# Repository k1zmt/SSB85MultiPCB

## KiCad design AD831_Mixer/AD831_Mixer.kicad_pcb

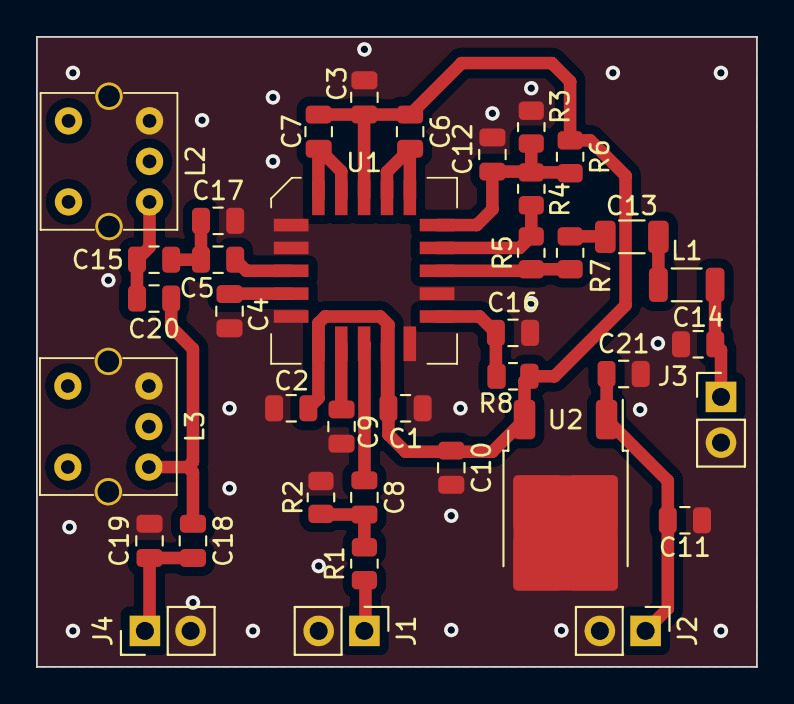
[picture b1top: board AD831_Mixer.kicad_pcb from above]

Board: 2 copper layers, 40.0 x 35.0 mm, 38 parts (0 on the bottom side), 22 nets.

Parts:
C1, C2, C3, C4, C5, C6, C7, C8, C9, C11, C12, C14, C16: 104; C_0805_2012Metric
C10, C21: 105; C_0805_2012Metric
C13: 104; C_1206_3216Metric
C15, C18: 820; C_0805_2012Metric
C17, C19: 751; C_0805_2012Metric
C20: 7.5p; C_0805_2012Metric
J1, J4: Conn_Coaxial; PinHeader_1x02_P2.54mm_Vertical
J2, J3: Conn_01x02; PinHeader_1x02_P2.54mm_Vertical
L1: L_Ferrite; L_1206_3216Metric
L2, L3: L_Core_Ferrite_Coupled_12345; L_Coilcraft_Slot7_15
R1: 221; R_0805_2012Metric
R2: 510; R_0805_2012Metric
R3, R6, R8: 472; R_0805_2012Metric
R4: 51R; R_0805_2012Metric
R5: 111; R_0805_2012Metric
R7: 102; R_0805_2012Metric
U1: AD831AP; PLCC-20
U2: LM78M05_TO252; TO-252-2

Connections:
+9V: C1.2, C2.2, C3.2, C6.1, C7.1, C10.1, R6.1, R8.2, U1.1 (VP), U1.9 (VP), U1.12 (VP), U2.3 (VO)
Earth: C1.1, C2.1, C3.1, C4.2, C9.2, C10.2, C11.2, C12.2, C14.2, C16.2, C17.2, C19.2, C21.2, J1.2 (Ext), J2.2, J3.2, J4.2 (Ext), L2.3, L2.MP, L3.3, L3.MP, R2.1, R3.1, U1.4 (GND), U1.5 (VN), U1.8 (VN), U1.13 (GND), U1.15 (VN), U2.2 (GND)
unnamed: C8.1, R1.2, R2.2
unnamed: C13.1, L1.1
unnamed: C13.2, R7.1
unnamed: C15.1, C20.2, L2.1
unnamed: C5.2, C15.2, C17.1
unnamed: C18.1, C20.1, L3.1
unnamed: J1.1 (In), R1.1
unnamed: C11.1, C21.1, J2.1, U2.1 (VI)
unnamed: C14.1, J3.1, L1.2
unnamed: C18.2, C19.1, J4.1 (In)
unnamed: C7.2, U1.2 (IFN), U1.3 (AN)
unnamed: C6.2, U1.19 (AP), U1.20 (IFP)
unnamed: C16.1, R8.1, U1.14 (BIAS)
unnamed: C12.1, R3.2, R4.1, R6.2, U1.18 (COM)
unnamed: C9.1, U1.10 (LON)
unnamed: C8.2, U1.11 (LOP)
unnamed: R5.2, R7.2, U1.16 (OUT)
unnamed: C4.1, U1.7 (RFN)
unnamed: C5.1, U1.6 (RFP)
unnamed: R4.2, R5.1, U1.17 (VFB)

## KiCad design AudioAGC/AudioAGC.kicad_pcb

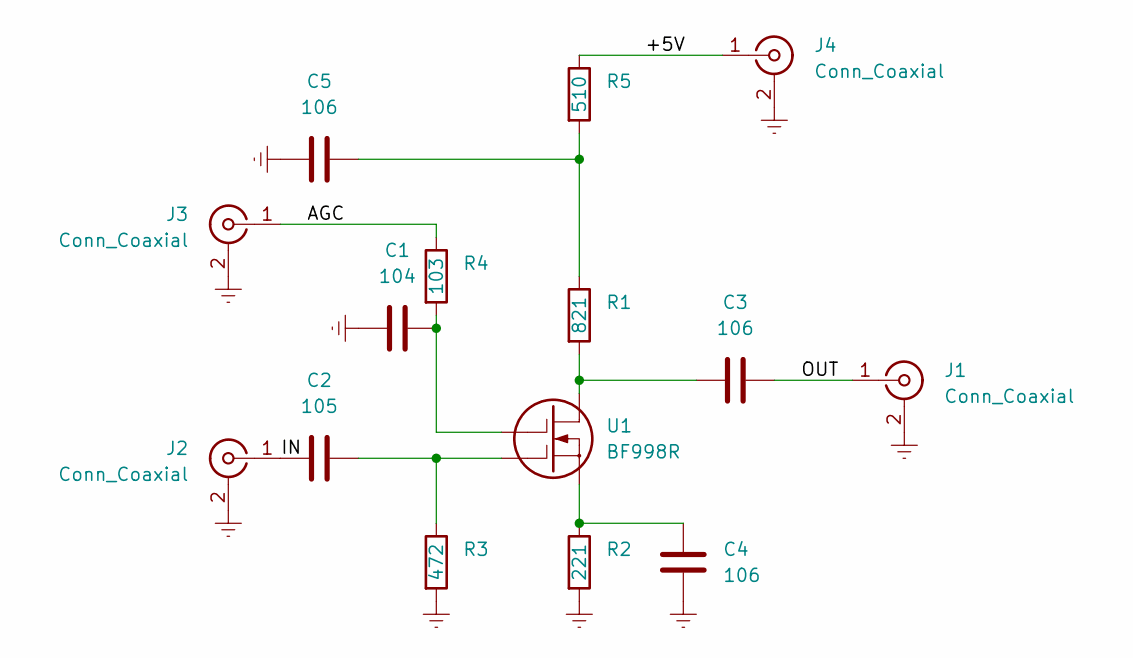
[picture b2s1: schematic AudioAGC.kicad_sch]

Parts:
C1: 104; C_0805_2012Metric
C2: 105; C_0805_2012Metric
C3, C4, C5: 106; C_0805_2012Metric
J1, J2, J3, J4: Conn_Coaxial; U.FL_Hirose_U.FL-R-SMT-1_Vertical
R1: 821; R_0805_2012Metric
R2: 221; R_0805_2012Metric
R3: 472; R_0805_2012Metric
R4: 103; R_0805_2012Metric
R5: 510; R_0805_2012Metric
U1: BF998R; SOT-143R

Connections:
/+5V: J4.1 (In), R5.1
/AGC: J3.1 (In), R4.1
/IN: C2.1, J2.1 (In)
/OUT: C3.2, J1.1 (In)
Earth: C1.1, C4.1, C5.1, J1.2 (Ext), J2.2 (Ext), J3.2 (Ext), J4.2 (Ext), R2.2, R3.2
unnamed: C5.2, R1.1, R5.2
unnamed: C3.1, R1.2, U1.2 (D)
unnamed: C2.2, R3.1, U1.4 (G1)
unnamed: C1.2, R4.2, U1.3 (G2)
unnamed: C4.2, R2.1, U1.1 (S)

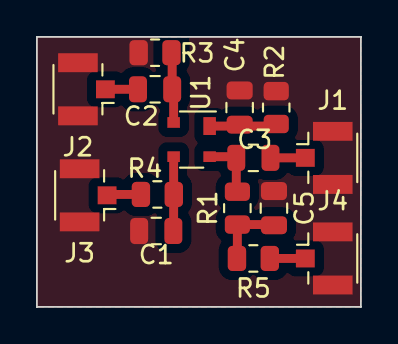
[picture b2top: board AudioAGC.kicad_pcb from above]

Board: 2 copper layers, 18.0 x 15.0 mm, 15 parts (0 on the bottom side), 10 nets.

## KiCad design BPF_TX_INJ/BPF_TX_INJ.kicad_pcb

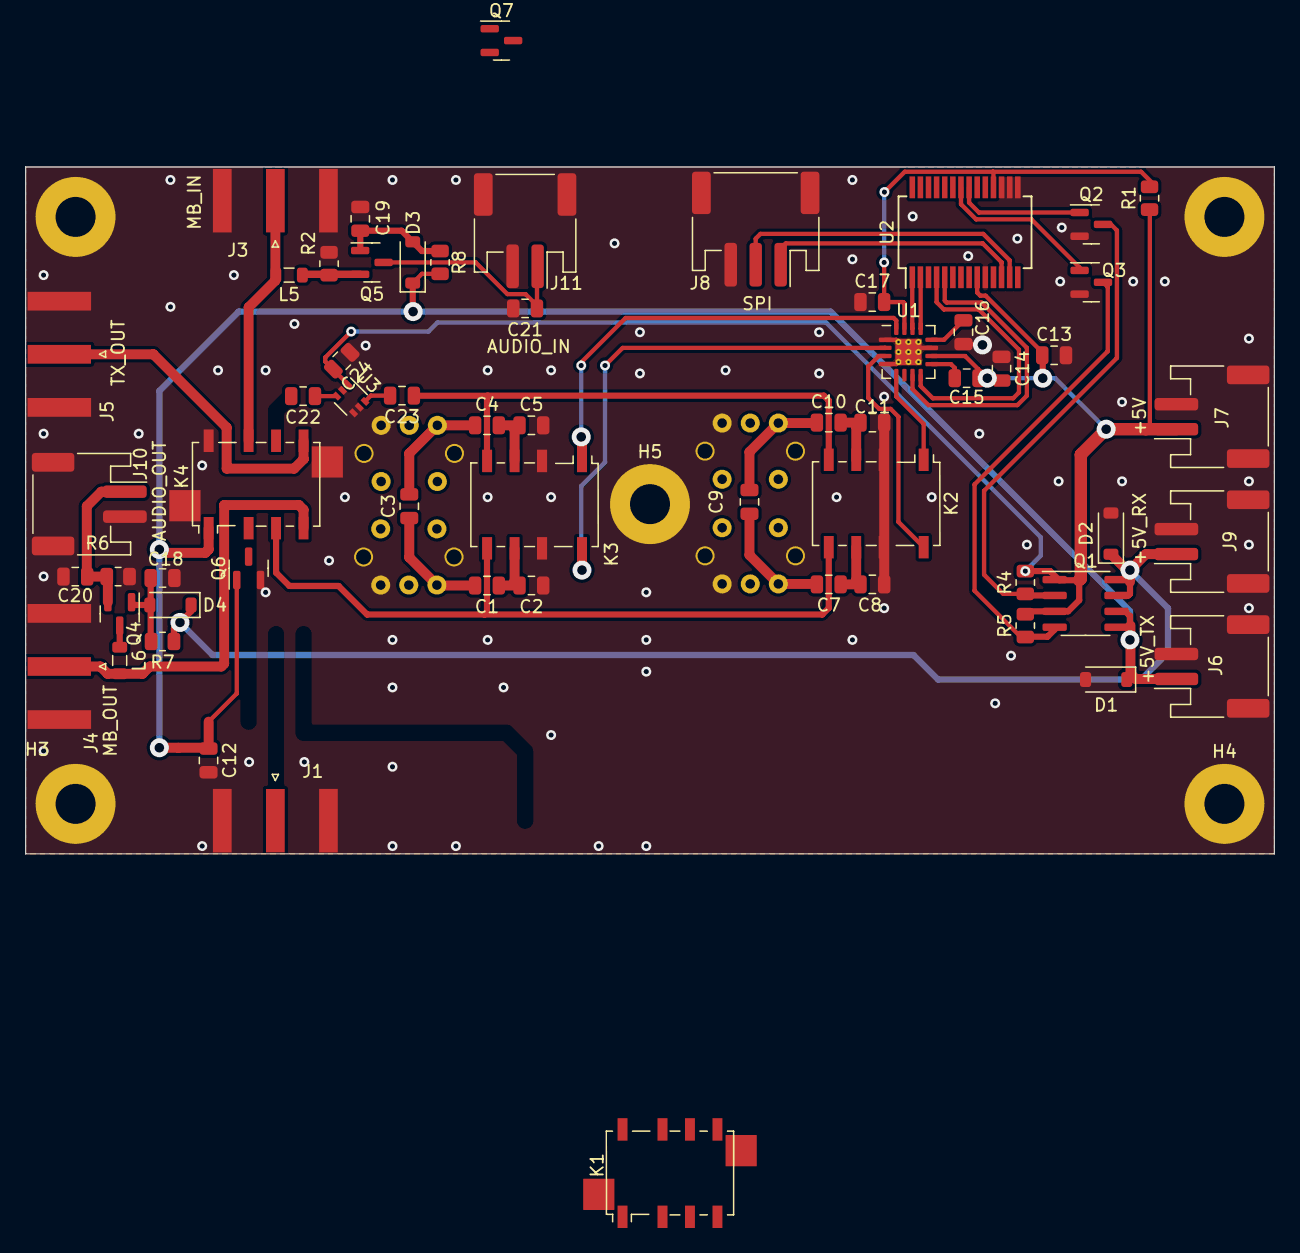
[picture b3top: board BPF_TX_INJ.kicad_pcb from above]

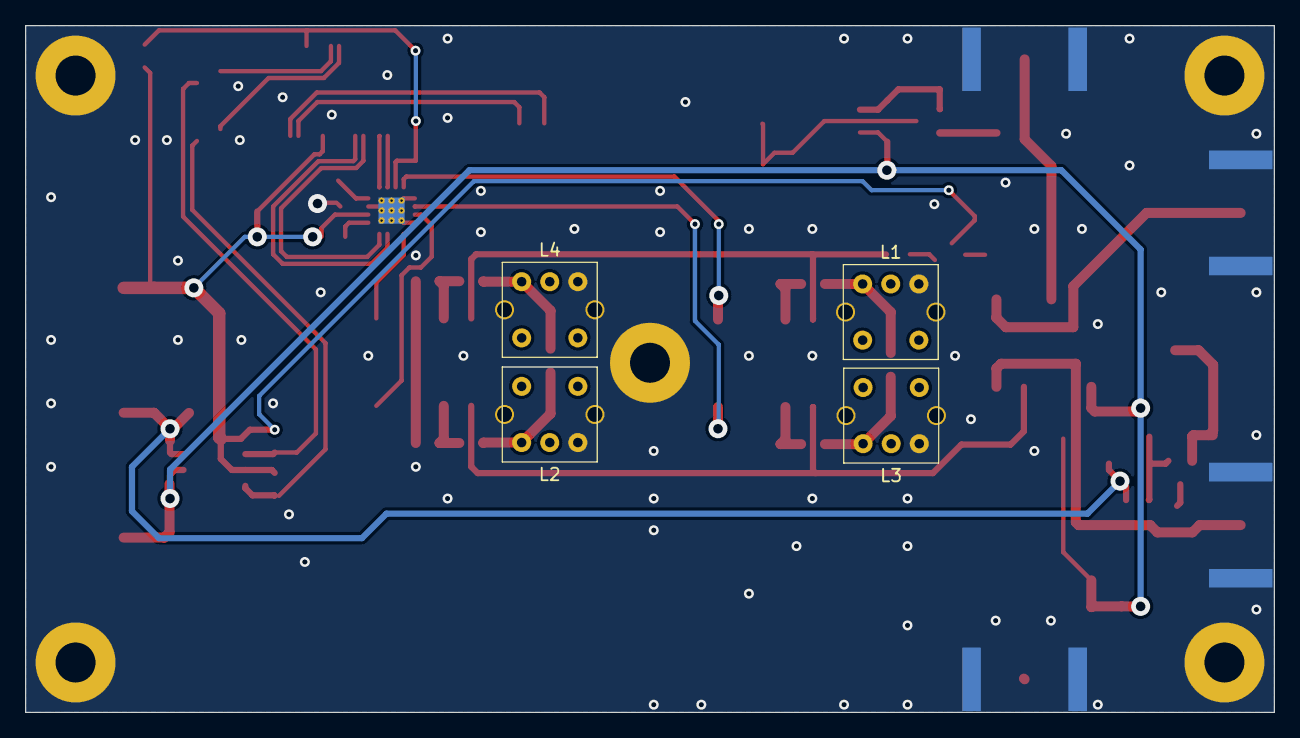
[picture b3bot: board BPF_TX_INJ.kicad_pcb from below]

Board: 2 copper layers, 100.0 x 55.0 mm, 69 parts (4 on the bottom side), 49 nets.

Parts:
C1, C4: 180p; C_0805_2012Metric
C2, C5: 820p; C_0805_2012Metric
C3: 8p; C_0805_2012Metric
C7, C10: 27p; C_0805_2012Metric
C8, C11: 100p; C_0805_2012Metric
C9: 2.7p; C_0805_2012Metric
C12, C13, C14, C15, C17, C18, C19, C24: 104; C_0805_2012Metric
C16: 106; C_0805_2012Metric
C20, C21, C22, C23: 103; C_0805_2012Metric
D1, D2, D3, D4: 1N4148W; D_SOD-123
H1, H2, H3, H4, H5: MH; MountingHole_3.2mm_M3_Pad
J1: RX_IN; SMA_Amphenol_132289_EdgeMount
J3: MB_IN; SMA_Amphenol_132289_EdgeMount
J4: MB_OUT; SMA_Amphenol_132289_EdgeMount
J5: TX_OUT; SMA_Amphenol_132289_EdgeMount
J6: +5V_TX; JST_PH_S2B-PH-SM4-TB_1x02-1MP_P2.00mm_Horizontal
J7: +5V; JST_PH_S2B-PH-SM4-TB_1x02-1MP_P2.00mm_Horizontal
J8: SPI; JST_PH_S3B-PH-SM4-TB_1x03-1MP_P2.00mm_Horizontal
J9: +5V_RX; JST_PH_S2B-PH-SM4-TB_1x02-1MP_P2.00mm_Horizontal
J10: AUDIO_OUT; JST_PH_S2B-PH-SM4-TB_1x02-1MP_P2.00mm_Horizontal
J11: AUDIO_IN; JST_PH_S2B-PH-SM4-TB_1x02-1MP_P2.00mm_Horizontal
K1, K4: G6K-2F-RF; Relay_DPDT_Omron_G6K-2F-RF
K2, K3: G6KU-2; Relay_DPDT_Omron_G6K-2F-Y
L1, L3: 10uHn; L_Coilcraft_Slot7_1_3
L2, L4: 1uHn; L_Coilcraft_Slot7_1_3
L5, L6: 100uHn; L_0805_2012Metric
Q1: IRF7324; SOIC-8_3.9x4.9mm_P1.27mm
Q2, Q3, Q4, Q5, Q6, Q7: BSS138; SOT-23
R1, R2, R4, R5, R6, R7, R8: 103; R_0805_2012Metric
U1: DRV8833RTY; Texas_S-PWQFN-N16_EP2.1x2.1mm_ThermalVias
U2: MCP23017_SS; SSOP-28_5.3x10.2mm_P0.65mm
U3: BGA2866; SOT-363_SC-70-6

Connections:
+5V: C13.1, C14.2, C15.2, C24.2, J7.1, K1.1, Q1.1 (S1), Q1.3 (S2), R1.1, R4.1, R5.1, U1.10 (VM), U2.9 (VDD), U3.1 (Vcc)
+5V_RX: D2.1 (K), D4.1 (K), J9.1, Q1.7 (D1), Q1.8 (D1), R7.2
+5V_TX: C12.1, D1.1 (K), D3.1 (K), J6.1, K4.1, Q1.5 (D2), Q1.6 (D2), Q6.1 (G), R8.1
/ANT_RX_P: J1.1 (In), K4.2, Q6.3 (D)
/A_IN: C21.2, J11.1, Q5.3 (D)
/A_OUT: C20.1, J10.1, Q4.2 (S), R6.1
/BPF_IN: K2.5, K3.5, K4.3
/MB_IN: J3.1 (In), K4.7, L5.2
/MB_OUT: J4.1 (In), K4.4, L6.2
/R10M: K2.8, U1.3 (BOUT2)
/R80M: K3.8, U1.2 (AOUT2)
/R_10M: U1.8 (BIN2), U2.4 (GPB3)
/R_80M: U1.13 (AIN2), U2.2 (GPB1)
/S10M: K2.1, U1.5 (BOUT1)
/S80M: K3.1, U1.16 (AOUT1)
/S_10M: U1.7 (BIN1), U2.5 (GPB4)
/S_80M: U1.14 (AIN1), U2.1 (GPB0)
/TX_OUT: J5.1 (In), K4.5
Earth: C2.2, C5.2, C8.2, C11.2, C12.2, C13.2, C14.1, C16.1, C17.1, C18.2, C19.2, C20.2, C21.1, C24.1, D1.2 (A), D2.2 (A), H1.1, H2.1, H3.1, H4.1, H5.1, J1.2 (Ext), J3.2 (Ext), J4.2 (Ext), J5.2 (Ext), J6.2, J6.MP (MountPin), J7.2, J7.MP (MountPin), J8.3, J8.MP (MountPin), J9.2, J9.MP (MountPin), J10.2, J10.MP (MountPin), J11.2, J11.MP (MountPin), K1.9, K2.2, K2.7, K3.2, K3.7, K4.8, K4.9, L1.1, L1.MP, L2.2, L2.MP, L3.2, L3.MP, L4.1, L4.MP, Q2.2 (S), Q3.2 (S), Q6.2 (S), Q7.2 (S), R2.2, R6.2, U1.1 (AISEN), U1.4 (BISEN), U1.11 (GND), U1.17 (GND(PPAD)), U2.10 (VSS), U2.15 (A0), U2.16 (A1), U2.17 (A2), U3.2 (G), U3.4 (G), U3.5 (G)
unnamed: C1.1, C3.1, L3.1
unnamed: C1.2, C2.1, K3.6
unnamed: C3.2, C4.1, L1.2
unnamed: C4.2, C5.1, K3.3
unnamed: C7.1, C9.1, L2.1
unnamed: C7.2, C8.1, K2.6
unnamed: C9.2, C10.1, L4.2
unnamed: C10.2, C11.1, K2.3
unnamed: C22.1, U3.3
unnamed: C22.2, K1.4
unnamed: C23.1, K1.5
unnamed: C23.2, U3.6
unnamed: C19.1, D3.2 (A), Q5.1 (G), R8.2
unnamed: C18.1, D4.2 (A), Q4.1 (G), R7.1
unnamed: K1.2, K1.7
unnamed: K1.3, K4.6
unnamed: K1.6, K2.4, K3.4
unnamed: Q1.2 (G1), Q2.3 (D), R4.2
unnamed: Q1.4 (G2), Q3.3 (D), R5.2
unnamed: Q2.1 (G), U2.21 (GPA0)
unnamed: Q3.1 (G), U2.22 (GPA1)
unnamed: L6.1, Q4.3 (D)
unnamed: L5.1, Q5.2 (S), R2.1
unnamed: K1.8, Q7.3 (D)
unnamed: C15.1, U1.9 (VCP)
unnamed: C16.2, U1.12 (VINT)
unnamed: C17.2, R1.2, U1.15 (nSLEEP), U2.18 (~RESET)
PREAMP: Q7.1 (G), U2.23 (GPA2)
SCL: J8.1, U2.12 (SCK)
SDA: J8.2, U2.13 (SDA)

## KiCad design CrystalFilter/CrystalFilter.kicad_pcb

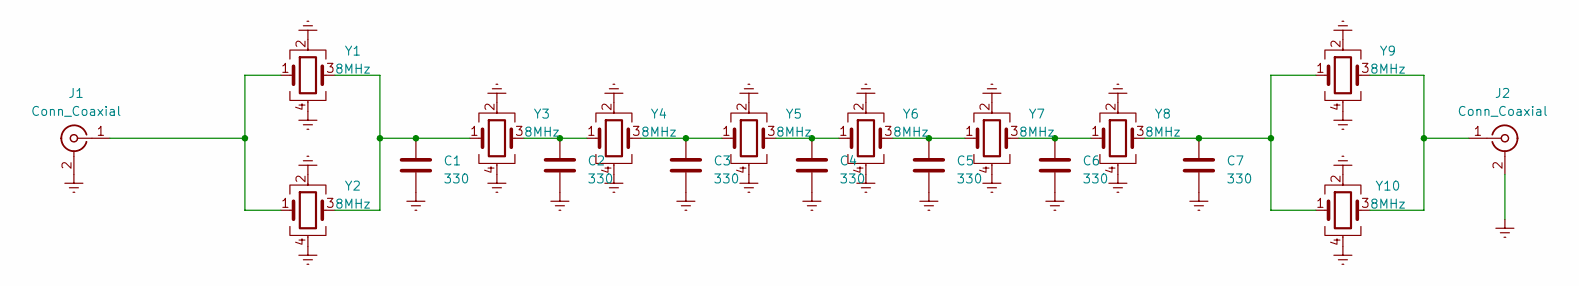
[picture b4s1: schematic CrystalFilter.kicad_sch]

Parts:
C1, C2, C3, C4, C5, C6, C7: 330; C_0805_2012Metric
J1, J2: Conn_Coaxial; U.FL_Hirose_U.FL-R-SMT-1_Vertical
Y1, Y2, Y3, Y4, Y5, Y6, Y7, Y8, Y9, Y10: 8MHz; Crystal_SMD_3225-4Pin_3.2x2.5mm

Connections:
Earth: C1.1, C2.1, C3.1, C4.1, C5.1, C6.1, C7.1, J1.2 (Ext), J2.2 (Ext), Y1.2, Y1.4, Y2.2, Y2.4, Y3.2, Y3.4, Y4.2, Y4.4, Y5.2, Y5.4, Y6.2, Y6.4, Y7.2, Y7.4, Y8.2, Y8.4, Y9.2, Y9.4, Y10.2, Y10.4
unnamed: C1.2, Y1.3, Y2.3, Y3.1
unnamed: C2.2, Y3.3, Y4.1
unnamed: C3.2, Y4.3, Y5.1
unnamed: C4.2, Y5.3, Y6.1
unnamed: C5.2, Y6.3, Y7.1
unnamed: C6.2, Y7.3, Y8.1
unnamed: C7.2, Y8.3, Y9.1, Y10.1
unnamed: J1.1 (In), Y1.1, Y2.1
unnamed: J2.1 (In), Y9.3, Y10.3

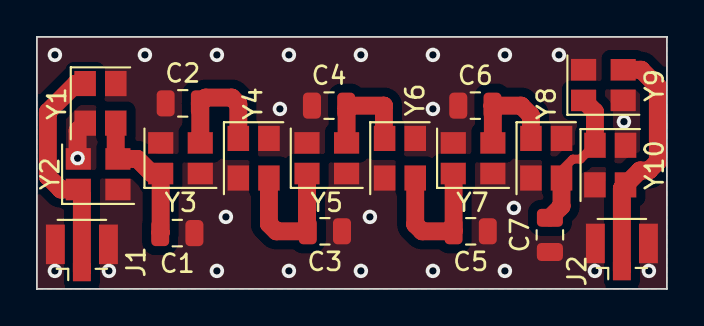
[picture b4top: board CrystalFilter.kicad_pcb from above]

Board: 2 copper layers, 35.0 x 14.0 mm, 19 parts (0 on the bottom side), 10 nets.

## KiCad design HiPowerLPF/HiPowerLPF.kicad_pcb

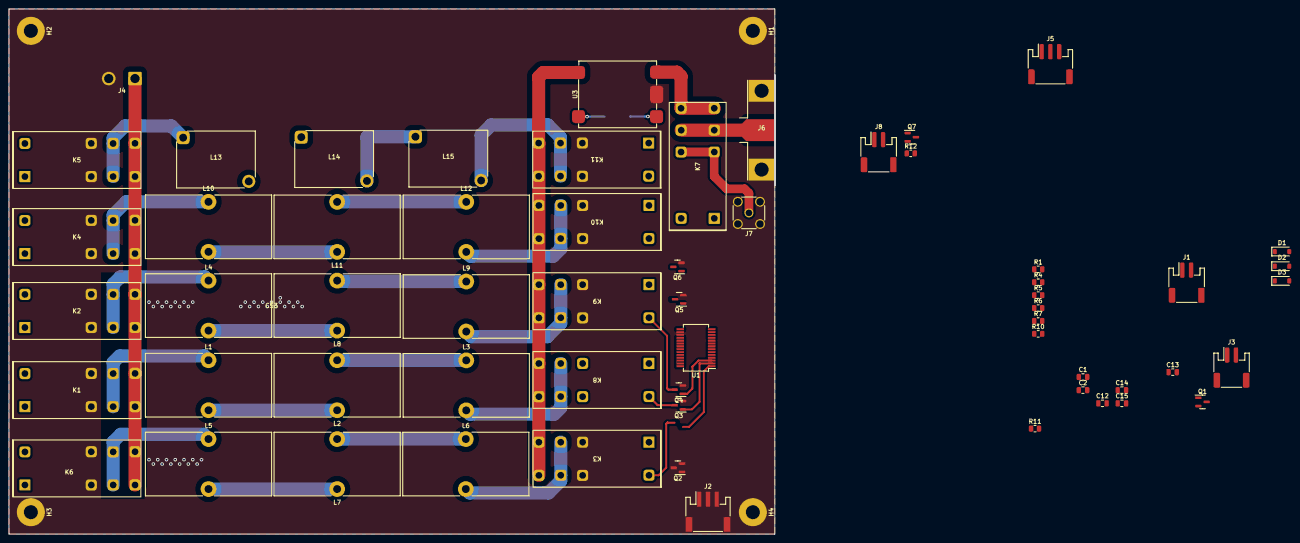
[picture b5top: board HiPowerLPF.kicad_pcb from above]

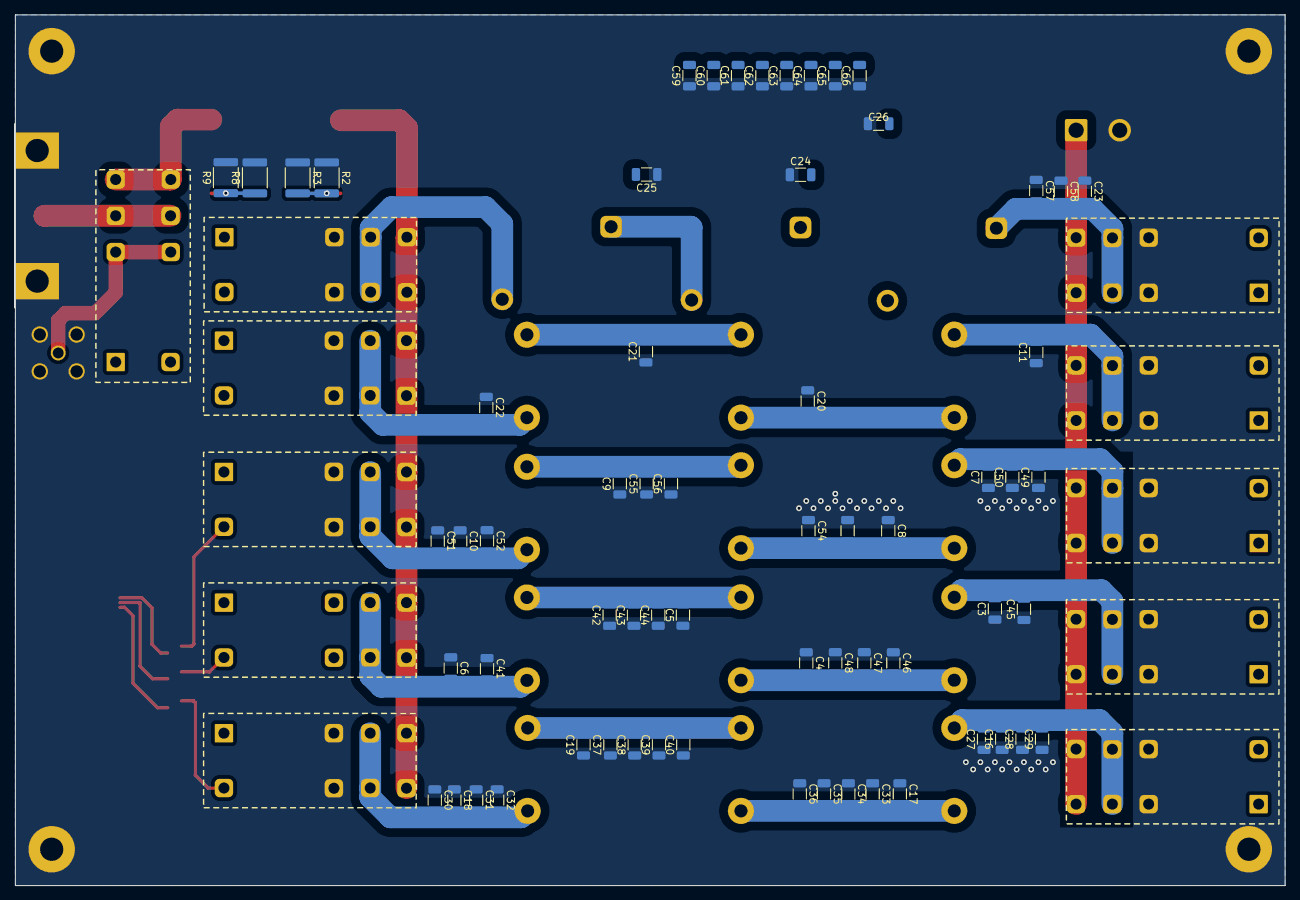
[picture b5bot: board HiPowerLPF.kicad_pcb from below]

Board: 2 copper layers, 175.0 x 120.0 mm, 128 parts (64 on the bottom side), 52 nets.

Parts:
C1, C2, C12, C13, C14, C15: 104; C_0805_2012Metric
C3, C4, C5, C6, C16, C27, C28, C29, C41, C42, C43, C45, C46, C47: 470p; C_1206_3216Metric
C7, C9, C49, C51, C52, C54: 220p; C_1206_3216Metric
C8, C53, C55, C56: 330p; C_1206_3216Metric
C10, C50, C57, C58, C60, C61, C62, C63, C65, C66: 47p; C_1206_3216Metric
C11, C22: 182; C_1206_3216Metric
C17, C19, C33, C34, C35, C36, C37, C38, C39, C40: 680p; C_1206_3216Metric
C18, C30, C31, C32: 470; C_1206_3216Metric
C20, C21: 332; C_1206_3216Metric
C23, C64: 33p; C_1206_3216Metric
C24, C25, C26, C59: 68p; C_1206_3216Metric
C44, C48: 100p; C_1206_3216Metric
D1: 1N4148W; D_SOD-123
D2, D3: D; D_SOD-123
H1, H2, H3, H4: MH; MountingHole_3.2mm_M3_Pad
J1: +5V; JST_PH_S2B-PH-SM4-TB_1x02-1MP_P2.00mm_Horizontal
J2: SPI; JST_PH_S3B-PH-SM4-TB_1x03-1MP_P2.00mm_Horizontal
J3: +5V_TX; JST_PH_S2B-PH-SM4-TB_1x02-1MP_P2.00mm_Horizontal
J4: TX_AMP_IN; SolderWire-1.5sqmm_1x02_P6mm_D1.7mm_OD3mm
J5: Conn_01x03_MountingPin; JST_PH_S3B-PH-SM4-TB_1x03-1MP_P2.00mm_Horizontal
J6: ANTENNA; Connector_SO239
J7: RX_BPF; SMA_Amphenol_132291_Vertical
J8: +12V; JST_PH_S2B-PH-SM4-TB_1x02-1MP_P2.00mm_Horizontal
K1, K2, K3, K4, K5, K6, K7, K8, K9, K10, K11: QJC2; Relay_QJC2
L1, L3: 2.7uH; L_Toroid_Vertical_L28.6mm_W14.3mm_P11.43mm_Bourns_5700
L2: 3.3uH; L_Toroid_Vertical_L28.6mm_W14.3mm_P11.43mm_Bourns_5700
L4, L9: 1.5uH; L_Toroid_Vertical_L28.6mm_W14.3mm_P11.43mm_Bourns_5700
L5, L6, L10, L12: 5.6uH; L_Toroid_Vertical_L28.6mm_W14.3mm_P11.43mm_Bourns_5700
L7, L11: 6.2uH; L_Toroid_Vertical_L28.6mm_W14.3mm_P11.43mm_Bourns_5700
L8: 1.6uH; L_Toroid_Vertical_L28.6mm_W14.3mm_P11.43mm_Bourns_5700
L13, L15: 390nH; L_AirCore_L15_P15mm
L14: 430nH; L_AirCore_L15_P15mm
Q1: BSS138; SOT-23
Q2, Q3, Q4, Q5, Q6, Q7: AO3400A; SOT-23
R1: 103; R_0805_2012Metric
R2, R3, R8, R9: 101; R_1812_4532Metric
R4, R7: 223; R_0805_2012Metric
R5, R6, R10, R12: 102; R_0805_2012Metric
R11: 104; R_0805_2012Metric
U1: MCP23017_SS; SSOP-28_5.3x10.2mm_P0.65mm
U3: 1T:20T, BN-43-202; Balun_5PIN_BN-43-202_SMD_SWR_Bridge

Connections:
+5V: C2.1, J1.1, R1.1, U1.9 (VDD)
+5V_TX: D1.1 (K), J3.1, R10.1, R12.1
+12V: C15.1, J8.1, K1.1, K2.1, K3.1, K4.1, K5.1, K6.1, K7.1, K8.1, K9.1, K11.1
/ANT: J6.1 (In), K7.3, K7.6, R11.2
/FWD: J5.1, R5.2
/Filter10M/FLT30MHZ_1: C23.2, C57.2, C58.2, K5.3, K5.6, L13.1
/Filter10M/FLT30MHZ_2: C24.2, C59.2, C60.2, C61.2, L13.2, L14.1
/Filter10M/FLT30MHZ_3: C25.2, C26.2, C65.2, C66.2, L14.2, L15.1
/Filter10M/FLT30MHZ_4: C62.2, C63.2, C64.2, K11.3, K11.6, L15.2
/Filter20M/FLT15MHZ_1: C11.2, K4.3, K4.6, L10.1
/Filter20M/FLT15MHZ_2: C20.2, L10.2, L11.1
/Filter20M/FLT15MHZ_3: C21.2, L11.2, L12.1
/Filter20M/FLT15MHZ_4: C22.2, K10.3, K10.6, L12.2
/Filter40M/FLT8MHZ_1: C7.2, C49.2, C50.2, K2.3, K2.6, L4.1
/Filter40M/FLT8MHZ_2: C8.2, C53.2, C54.2, L4.2, L8.1
/Filter40M/FLT8MHZ_3: C9.2, C55.2, C56.2, L8.2, L9.1
/Filter40M/FLT8MHZ_4: C10.2, C51.2, C52.2, K9.3, K9.6, L9.2
/Filter80M/FLT4MHZ_1: C3.2, C45.2, K1.3, K1.6, L1.1
/Filter80M/FLT4MHZ_2: C4.2, C46.2, C47.2, C48.2, L1.2, L2.1
/Filter80M/FLT4MHZ_3: C5.2, C42.2, C43.2, C44.2, L2.2, L3.1
/Filter80M/FLT4MHZ_4: C6.2, C41.2, K8.3, K8.6, L3.2
/Filter160M/FLT2MHZ_1: C16.2, C27.2, C28.2, C29.2, K6.3, K6.6, L5.1
/Filter160M/FLT2MHZ_2: C17.2, C33.2, C34.2, C35.2, C36.2, L5.2, L7.1
/Filter160M/FLT2MHZ_3: C19.2, C37.2, C38.2, C39.2, C40.2, L6.1, L7.2
/Filter160M/FLT2MHZ_4: C18.2, C30.2, C31.2, C32.2, K3.3, K3.6, L6.2
/REF: J5.3, R6.2
/RX: J7.1 (In), K7.2, K7.7, Q1.3 (D)
/SWR_OUT: K7.4, K7.5, U3.2 (OUT)
ACT_10: Q6.1 (G), U1.5 (GPB4)
ACT_20: Q5.1 (G), U1.4 (GPB3)
ACT_40: Q4.1 (G), U1.3 (GPB2)
ACT_80: Q3.1 (G), U1.2 (GPB1)
ACT_160: Q2.1 (G), U1.1 (GPB0)
Earth: C1.1, C2.2, C3.1, C4.1, C5.1, C6.1, C7.1, C8.1, C9.1, C10.1, C11.1, C12.2, C13.1, C14.2, C15.2, C16.1, C17.1, C18.1, C19.1, C20.1, C21.1, C22.1, C23.1, C24.1, C25.1, C26.1, C27.1, C28.1, C29.1, C30.1, C31.1, C32.1, C33.1, C34.1, C35.1, C36.1, C37.1, C38.1, C39.1, C40.1, C41.1, C42.1, C43.1, C44.1, C45.1, C46.1, C47.1, C48.1, C49.1, C50.1, C51.1, C52.1, C53.1, C54.1, C55.1, C56.1, C57.1, C58.1, C59.1, C60.1, C61.1, C62.1, C63.1, C64.1, C65.1, C66.1, D1.2 (A), H1.1, H2.1, H3.1, H4.1, J1.2, J1.MP (MountPin), J2.3, J2.MP (MountPin), J3.2, J3.MP (MountPin), J4.2 (Ext), J5.2, J5.MP (MountPin), J6.2 (Ext), J7.2 (Ext), K1.2, K1.7, K2.2, K2.7, K3.2, K3.7, K4.2, K4.7, K5.2, K5.7, K6.2, K6.7, K9.2, K9.7, K10.2, K10.7, K11.2, K11.7, Q1.2 (S), Q2.2 (S), Q3.2 (S), Q4.2 (S), Q5.2 (S), Q6.2 (S), Q7.2 (S), R2.1, R3.1, R4.1, R7.2, R8.2, R9.2, R11.1, U1.10 (VSS), U1.16 (A1), U1.17 (A2), U3.3 (COM)
FLT_IN: J4.1 (In), K1.4, K1.5, K2.4, K2.5, K4.4, K4.5, K5.4, K5.5, K6.4, K6.5
FLT_OUT: K3.4, K3.5, K8.4, K8.5, K9.4, K9.5, K10.4, K10.5, K11.4, K11.5, U3.1 (IN)
unnamed: D2.2 (A), R2.2, R3.2, U3.5 (FWD)
unnamed: C12.1, D2.1 (K), R4.2, R5.1
unnamed: D3.2 (A), R8.1, R9.1, U3.4 (REF)
unnamed: C13.2, D3.1 (K), R6.1, R7.1
unnamed: J8.2, J8.MP (MountPin)
unnamed: C14.1, Q1.1 (G), R10.2
unnamed: K3.8, K6.8, Q2.3 (D)
unnamed: K1.8, K8.8, Q3.3 (D)
unnamed: K2.8, K9.8, Q4.3 (D)
unnamed: K4.8, K10.8, Q5.3 (D)
unnamed: K5.8, K11.8, Q6.3 (D)
unnamed: K7.8, Q7.3 (D)
unnamed: Q7.1 (G), R12.2
unnamed: C1.2, R1.2, U1.15 (A0), U1.18 (~RESET)
SCL: J2.1, U1.12 (SCK)
SDA: J2.2, U1.13 (SDA)
